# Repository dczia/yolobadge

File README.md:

# yolobadge
Ziacon 2 / DefCon 29 #yolobadge 2021

A badge thought up, designed, and made in ~4 hours duing a live talk at ZiaCon 2, April 2021

Badge layout by @hamster  
Design input from @jediguybob @lithochasm and @DCZia  
Art from @LunaSylumDancer and Challenge from @Syntax  

```
             _       _               _            
 _   _  ___ | | ___ | |__   __ _  __| | __ _  ___ 
| | | |/ _ \| |/ _ \| '_ \ / _` |/ _` |/ _` |/ _ \
| |_| | (_) | | (_) | |_) | (_| | (_| | (_| |  __/
 \__, |\___/|_|\___/|_.__/ \__,_|\__,_|\__, |\___|
 |___/                                 |___/      

```

## Hardware

* ATMega 32U4 Microcontroller
* 10 Neopixel / WS2812B LED's
* Micro USB Power
* SAO Port
* Serial Breakout

## Software

Arduino Sketch using the FastLED libary to control the neopixels

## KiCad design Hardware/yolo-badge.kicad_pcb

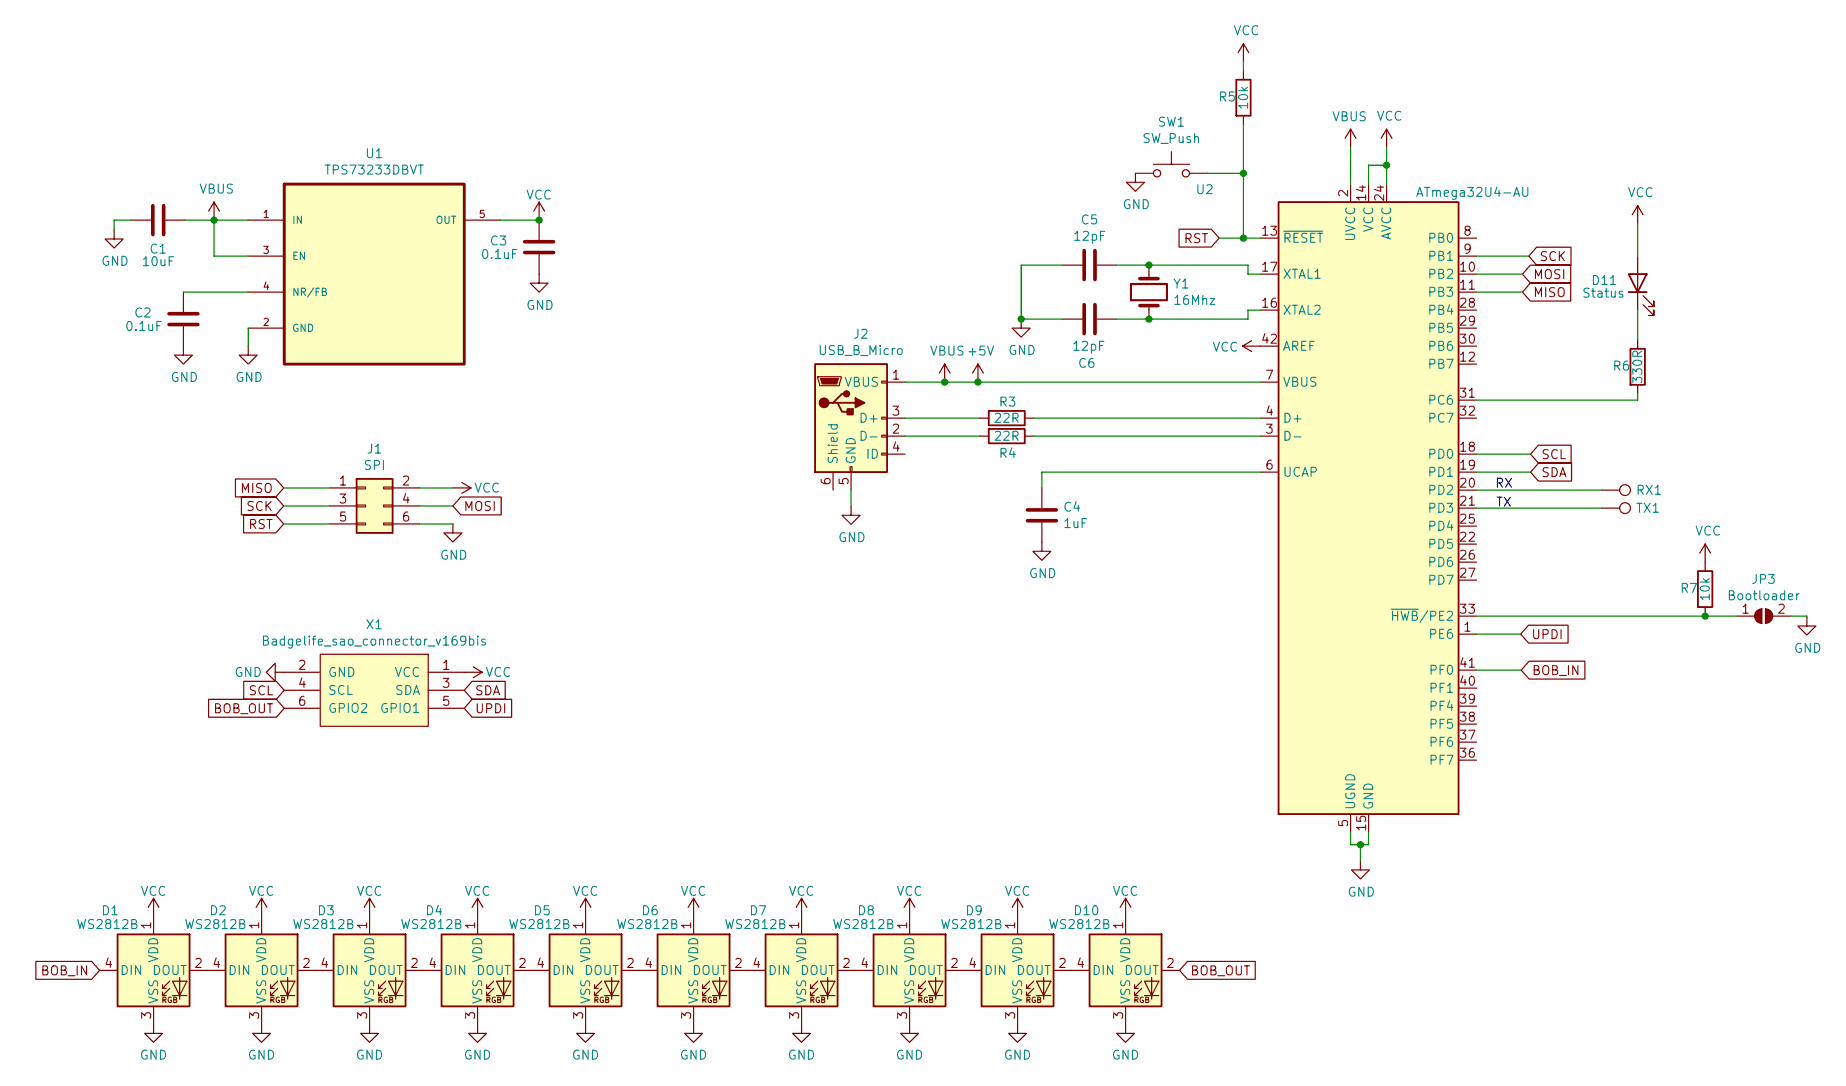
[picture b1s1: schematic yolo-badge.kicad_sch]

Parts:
C1: 10uF; C_0603_1608Metric
C2, C3: 0.1uF; C_0603_1608Metric
C4: 1uF; C_0603_1608Metric
C5, C6: 12pF; C_0603_1608Metric
D1, D2, D3, D4, D5, D6, D7, D8, D9, D10: WS2812B; LED_WS2812B_PLCC4_5.0x5.0mm_P3.2mm
D11: Status; LED_0603_1608Metric
J1: SPI; PinHeader_2x03_P2.54mm_Vertical
J2: USB_B_Micro; USB_Micro-B_Molex_47346-0001
JP3: Bootloader; SolderJumper-2_P1.3mm_Open_RoundedPad1.0x1.5mm
R3, R4: 22R; R_0603_1608Metric
R5, R7: 10k; R_0603_1608Metric
R6: 330R; R_0603_1608Metric
RX1: Test_Point; TestPoint_Pad_2.0x2.0mm
SW1: SW_Push; Wurth_434331013822
TX1: Test_Point; TestPoint_Pad_2.0x2.0mm
U1: TPS73233DBVT; SOT-23-5
U2: ATmega32U4-AU; TQFP-44_10x10mm_P0.8mm
X1: Badgelife_sao_connector_v169bis; Badgelife-Shitty-v1.69bis
Y1: 16Mhz; Crystal_SMD_HC49-SD

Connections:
+5V: C1.1, J2.1 (VBUS), U1.1 (IN), U1.3 (EN), U2.2 (UVCC), U2.7 (VBUS)
BOB_IN: D1.4 (DIN), U2.41 (PF0)
BOB_OUT: D10.2 (DOUT), X1.6 (GPIO2)
GND: C1.2, C2.1, C3.1, C4.2, C5.2, C6.2, D1.3 (VSS), D2.3 (VSS), D3.3 (VSS), D4.3 (VSS), D5.3 (VSS), D6.3 (VSS), D7.3 (VSS), D8.3 (VSS), D9.3 (VSS), D10.3 (VSS), J1.6, J2.5 (GND), JP3.2 (B), SW1.1, U1.2 (GND), U2.5 (UGND), U2.15 (GND), U2.23 (GND), U2.35 (GND), U2.43 (GND), X1.2 (GND)
MISO: J1.1, U2.11 (PB3)
MOSI: J1.4, U2.10 (PB2)
unnamed: C2.2, U1.4 (NR/FB)
unnamed: C4.1, U2.6 (UCAP)
unnamed: C5.1, U2.17 (XTAL1), Y1.2
unnamed: C6.1, U2.16 (XTAL2), Y1.1
unnamed: D1.2 (DOUT), D2.4 (DIN)
unnamed: D2.2 (DOUT), D3.4 (DIN)
unnamed: D3.2 (DOUT), D4.4 (DIN)
unnamed: D4.2 (DOUT), D5.4 (DIN)
unnamed: D5.2 (DOUT), D6.4 (DIN)
unnamed: D6.2 (DOUT), D7.4 (DIN)
unnamed: D7.2 (DOUT), D8.4 (DIN)
unnamed: D8.2 (DOUT), D9.4 (DIN)
unnamed: D9.2 (DOUT), D10.4 (DIN)
unnamed: D11.1 (K), R6.1
unnamed: J2.2 (D-), R4.2
unnamed: J2.3 (D+), R3.2
unnamed: JP3.1 (A), R7.2, U2.33 (~HWB~/PE2)
unnamed: R3.1, U2.4 (D+)
unnamed: R4.1, U2.3 (D-)
unnamed: R6.2, U2.31 (PC6)
unnamed: RX1.1, U2.20 (PD2)
unnamed: TX1.1, U2.21 (PD3)
RST: J1.5, R5.2, SW1.2, U2.13 (~RESET)
SCK: J1.3, U2.9 (PB1)
SCL: U2.18 (PD0), X1.4 (SCL)
SDA: U2.19 (PD1), X1.3 (SDA)
UPDI: U2.1 (PE6), X1.5 (GPIO1)
VCC: C3.2, D1.1 (VDD), D2.1 (VDD), D3.1 (VDD), D4.1 (VDD), D5.1 (VDD), D6.1 (VDD), D7.1 (VDD), D8.1 (VDD), D9.1 (VDD), D10.1 (VDD), D11.2 (A), J1.2, R5.1, R7.1, U1.5 (OUT), U2.14 (VCC), U2.24 (AVCC), U2.34 (VCC), U2.42 (AREF), U2.44 (AVCC), X1.1 (VCC)

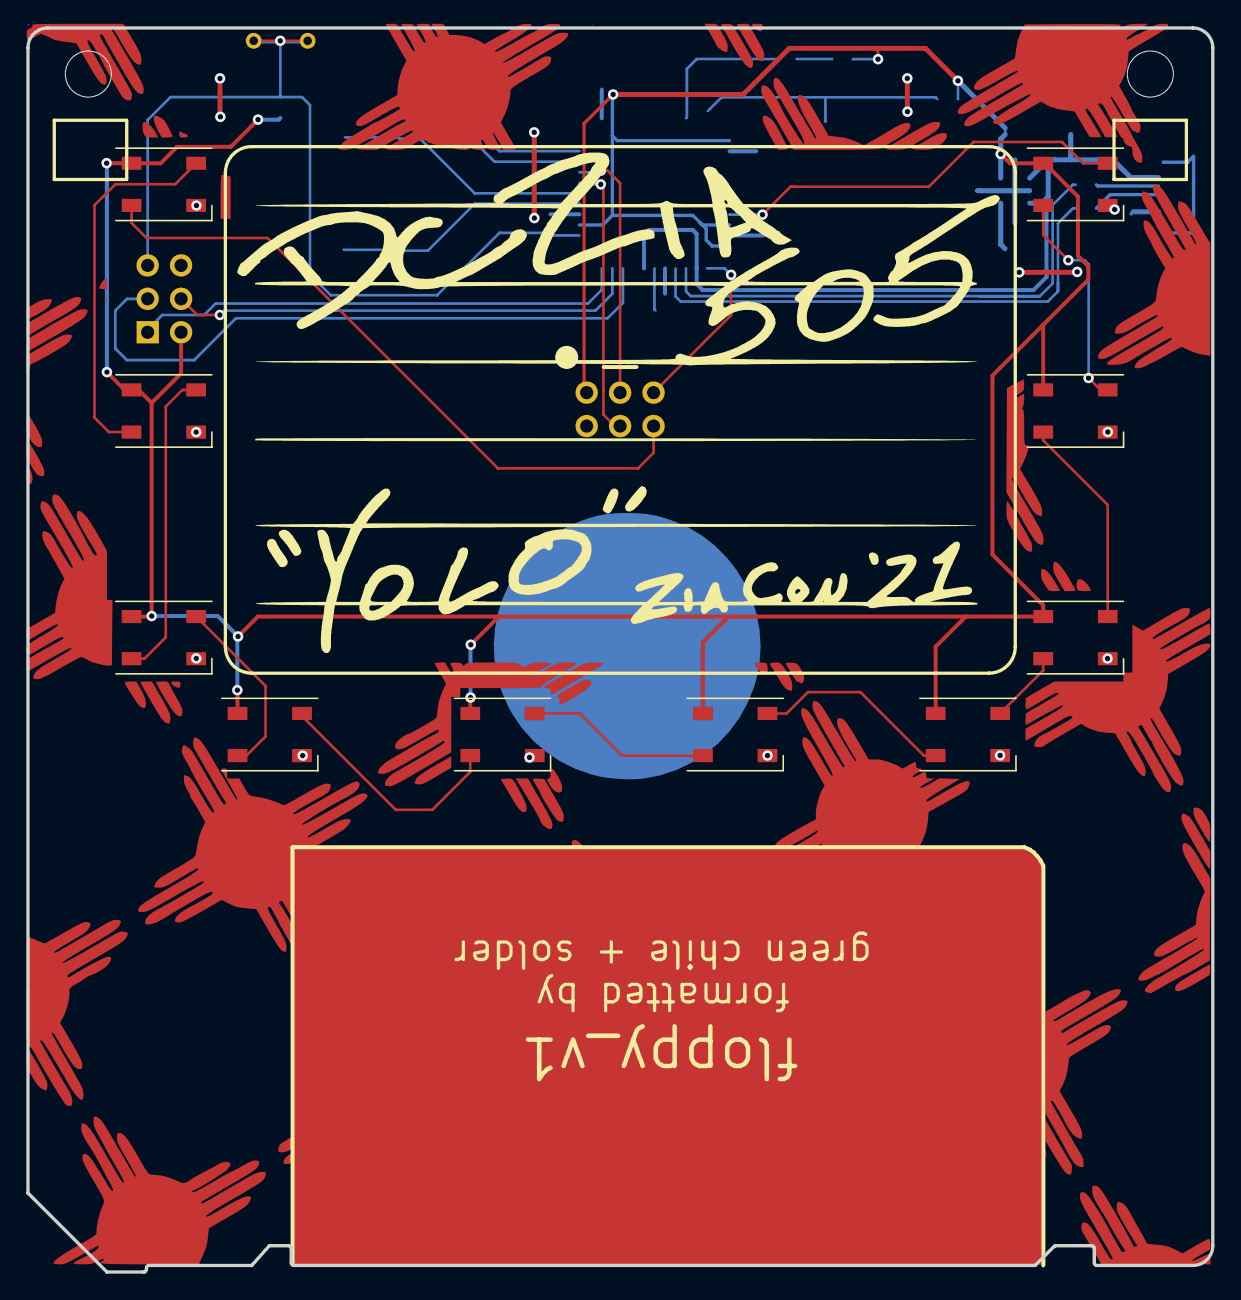
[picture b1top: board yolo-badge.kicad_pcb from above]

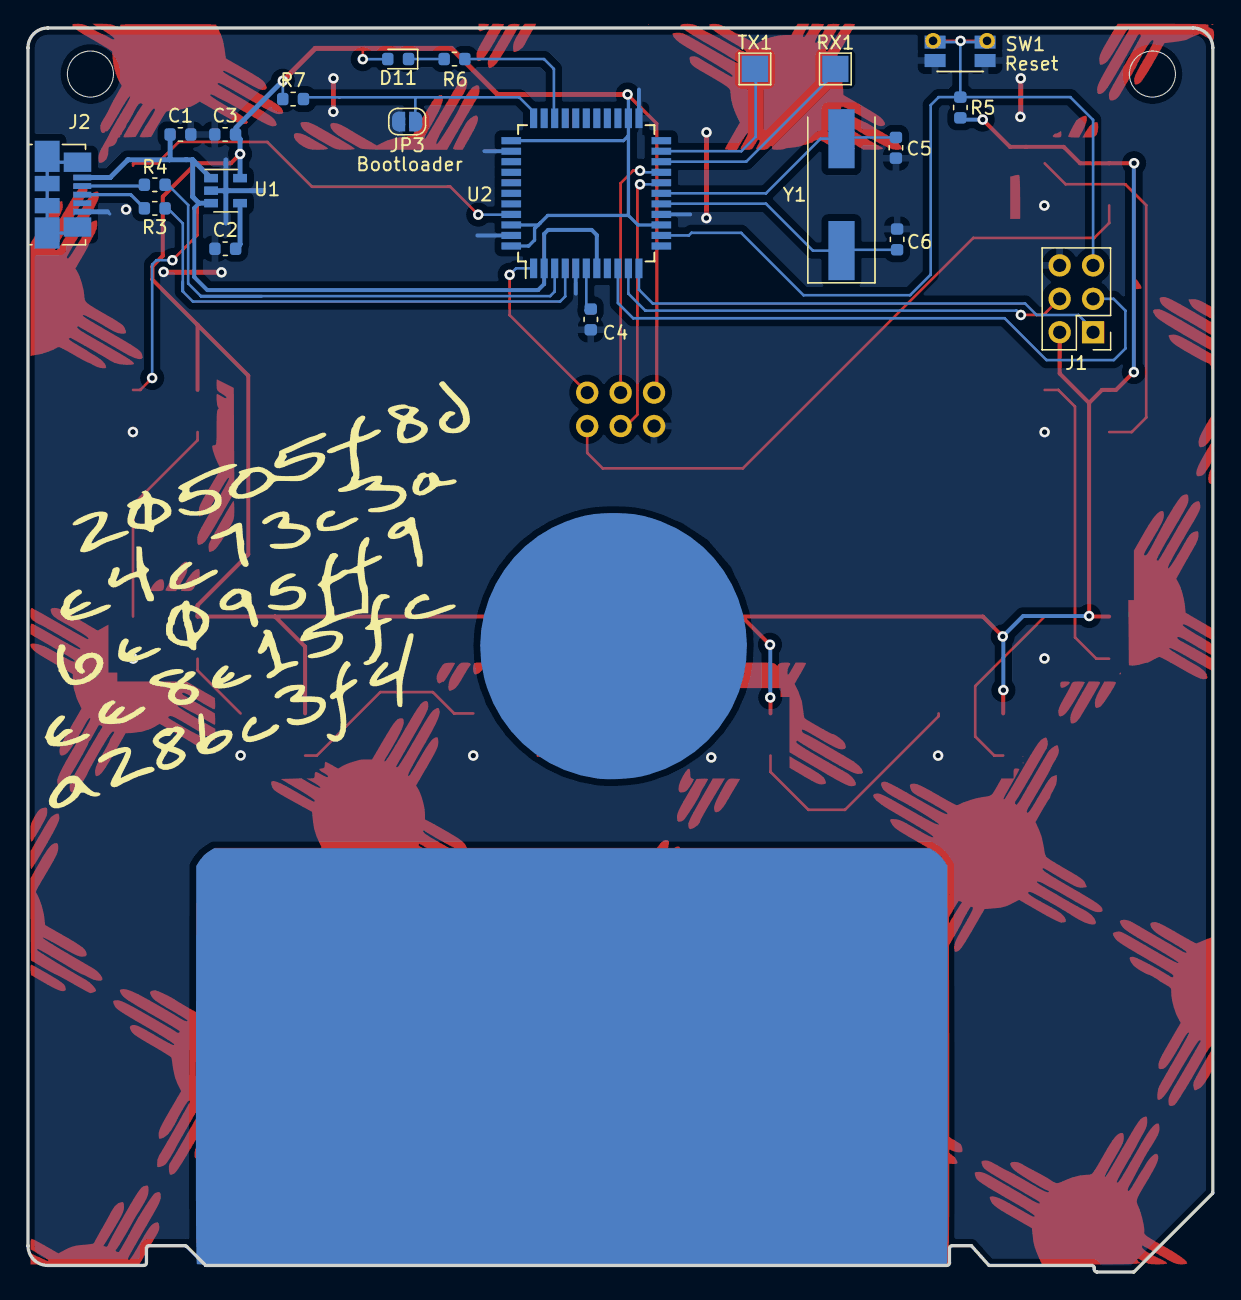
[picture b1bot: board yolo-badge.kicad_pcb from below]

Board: 2 copper layers, 90.0 x 94.5 mm, 32 parts (21 on the bottom side), 34 nets.

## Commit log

2021-05-10 Initial commit of the as-built rev 0 board
2021-07-22 Added initial lighting program
2021-07-22 Cleaned up swap file. (╯°□°)╯︵ ┻━┻
2021-07-23 Updated Readme, test lighting updates (not ready yet)
